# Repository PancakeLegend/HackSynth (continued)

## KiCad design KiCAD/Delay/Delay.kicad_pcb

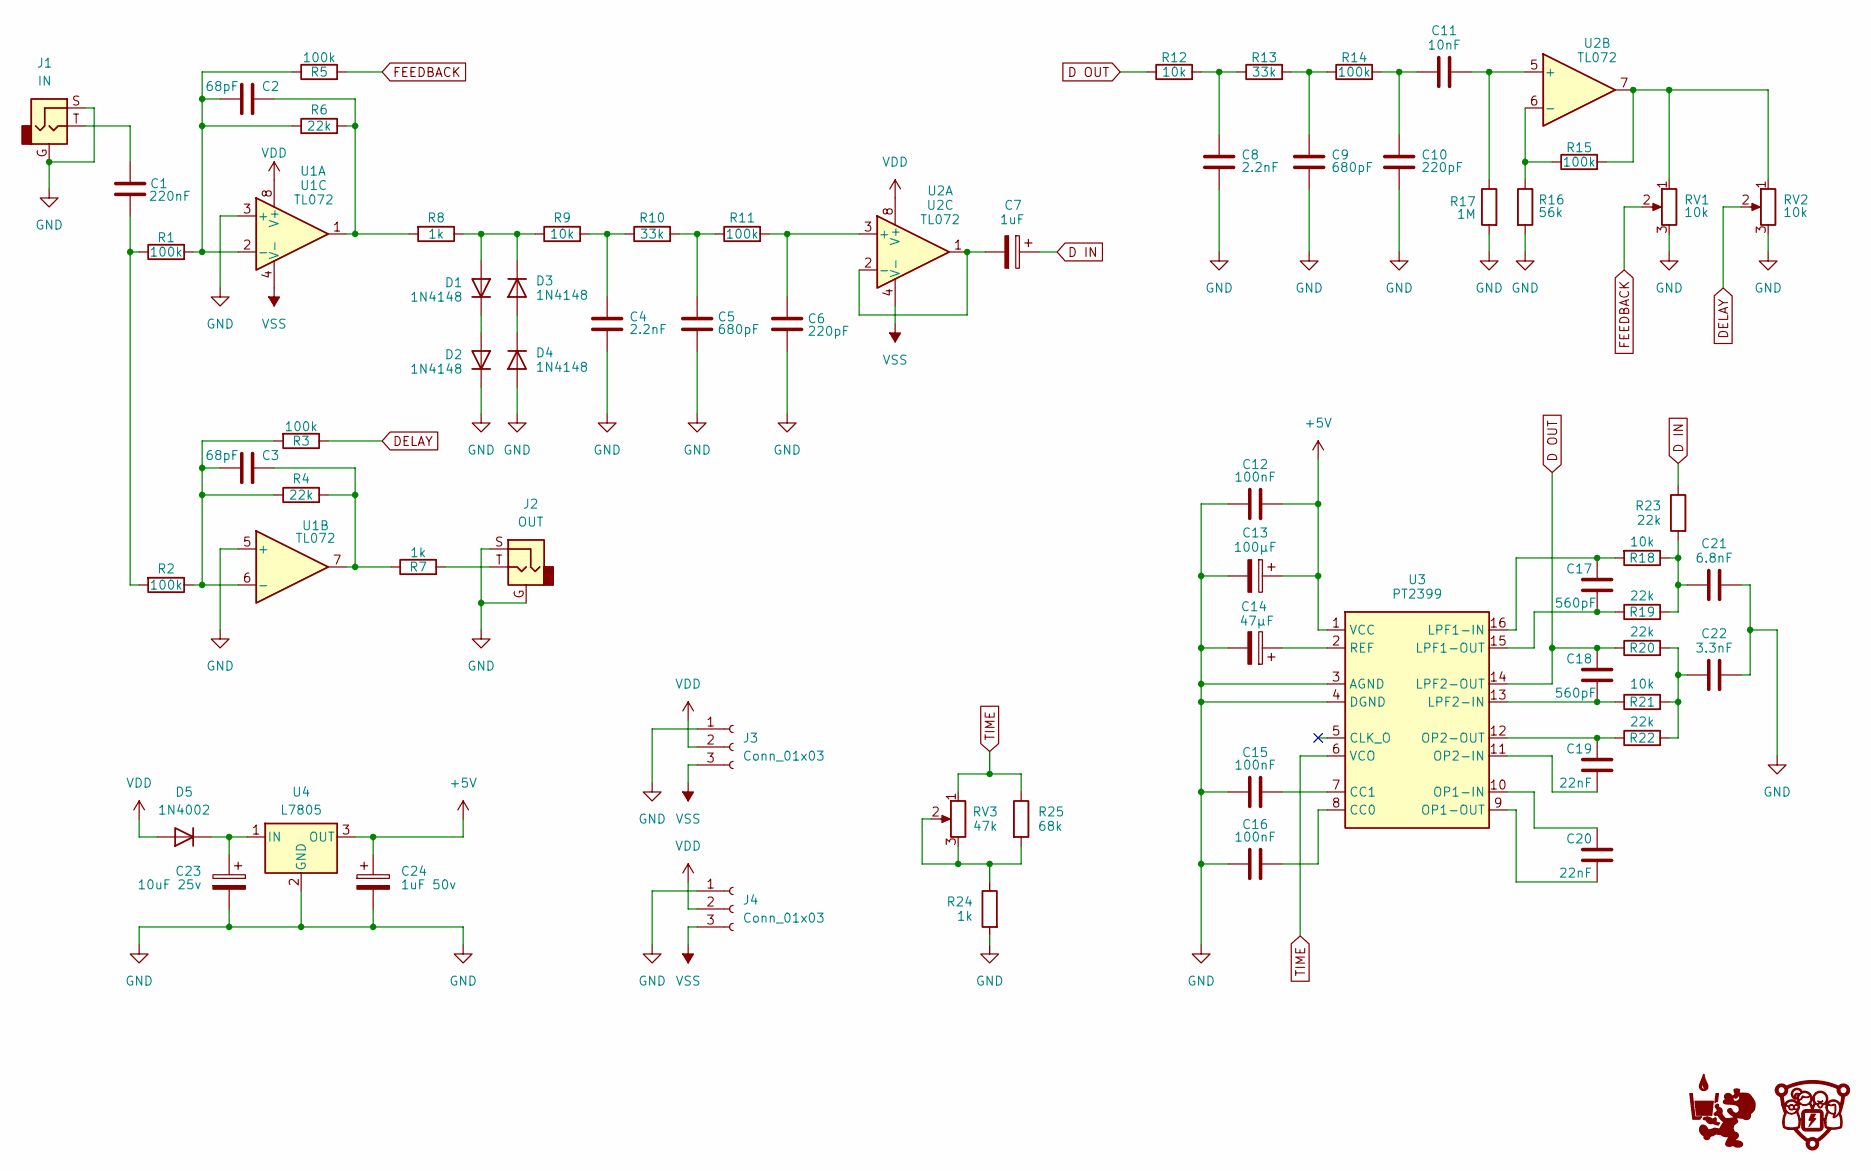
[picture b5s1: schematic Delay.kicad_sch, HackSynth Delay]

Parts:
C1: 220nF; C_Ceramic_D4.5mm_P5.00mm
C2, C3: 68pF; C_Ceramic_D4.5mm_P5.00mm
C4, C8: 2.2nF; C_Ceramic_D4.5mm_P5.00mm
C5, C9: 680pF; C_Ceramic_D4.5mm_P5.00mm
C6, C10: 220pF; C_Ceramic_D4.5mm_P5.00mm
C7: 1uF; CP_Radial_D4.0mm_P1.50mm
C11: 10nF; C_Ceramic_D4.5mm_P5.00mm
C12, C15, C16: 100nF; C_Ceramic_D4.5mm_P5.00mm
C13: 100µF; CP_Radial_D5.2mm_P2.50mm_LayDown_Mirror
C14: 47µF; CP_Radial_D5.2mm_P2.50mm_LayDown
C17, C18: 560pF; C_Ceramic_D4.5mm_P5.00mm
C19, C20: 22nF; C_Ceramic_D4.5mm_P5.00mm
C21: 6.8nF; C_Disc_D7.5mm_W5.0mm_P7.50mm
C22: 3.3nF; C_Disc_D7.5mm_W5.0mm_P7.50mm
C23: 10uF 25v; CP_Radial_D4.0mm_P1.50mm
C24: 1uF 50v; CP_Radial_D4.0mm_P1.50mm
D1, D2, D3, D4: 1N4148; D_Vertical_P2.54mm
D5: 1N4002; D_A-405_P7.62mm_Horizontal
G1, G2: (no value)
J1: IN; Jack_3.5mm
J2: OUT; Jack_3.5mm
J3, J4: Conn_01x03; JST_PH_S3B-PH-K_1x03_P2.00mm_Horizontal
R1, R2, R3, R5, R11, R14, R15: 100k; R_Vertical_P2.54mm
R4, R6, R19, R20, R22, R23: 22k; R_Vertical_P2.54mm
R7, R8, R24: 1k; R_Vertical_P2.54mm
R9, R12, R18, R21: 10k; R_Vertical_P2.54mm
R10, R13: 33k; R_Vertical_P2.54mm
R16: 56k; R_Vertical_P2.54mm
R17: 1M; R_Vertical_P2.54mm
R25: 68k; R_Vertical_P2.54mm
RV1, RV2: 10k; Potentiometer_Alps_RK09K_Horizontal
RV3: 47k; Potentiometer_Alps_RK09K_Horizontal
U1, U2: TL072; DIP-8_W7.62mm_LongPads
U3: PT2399; DIP-16_W7.62mm_LongPads
U4: L7805; L7805 - TO-220-3_Horizontal_TabDown

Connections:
+5V: C12.1, C13.1, C24.1, U3.1 (VCC), U4.3 (OUT)
D IN: C7.1, R23.1
D OUT: C18.1, R12.1, R20.1, U3.14 (LPF2-OUT)
DELAY: R3.1, RV2.2
FEEDBACK: R5.2, RV1.2
GND: C4.2, C5.2, C6.2, C8.2, C9.2, C10.2, C12.2, C13.2, C14.2, C15.2, C16.2, C21.1, C22.1, C23.2, C24.2, D2.1 (K), D4.2 (A), J1.G, J1.S, J2.G, J2.S, J3.1, J4.1, R16.2, R17.2, R24.2, RV1.3, RV2.3, U1.3 (+), U1.5 (+), U3.3 (AGND), U3.4 (DGND), U4.2 (GND)
unnamed: C1.1, R1.1, R2.2
unnamed: C1.2, J1.T
unnamed: C2.1, R6.2, R8.2, U1.1
unnamed: C3.1, R4.2, R7.1, U1.7
unnamed: C4.1, R9.2, R10.1
unnamed: C5.1, R10.2, R11.1
unnamed: C8.1, R12.2, R13.1
unnamed: C9.1, R13.2, R14.1
unnamed: C10.1, C11.1, R14.2
unnamed: C21.2, R18.1, R19.2, R23.2
unnamed: C22.2, R20.2, R21.2, R22.2
unnamed: D1.2 (A), D3.1 (K), R8.1, R9.1
unnamed: D1.1 (K), D2.2 (A)
unnamed: D3.2 (A), D4.1 (K)
unnamed: C23.1, D5.1 (K), U4.1 (IN)
unnamed: J2.T, R7.2
unnamed: R15.2, RV1.1, RV2.1, U2.7
unnamed: R24.1, R25.2, RV3.2, RV3.3
unnamed: C2.2, R1.2, R5.1, R6.1, U1.2 (-)
unnamed: C3.2, R2.1, R3.2, R4.1, U1.6 (-)
unnamed: C6.1, R11.2, U2.3 (+)
unnamed: C7.2, U2.1, U2.2 (-)
unnamed: C11.2, R17.1, U2.5 (+)
unnamed: R15.1, R16.1, U2.6 (-)
unnamed: C16.1, U3.8 (CC0)
unnamed: C15.1, U3.7 (CC1)
unnamed: C17.1, R18.2, U3.16 (LPF1-IN)
unnamed: C17.2, R19.1, U3.15 (LPF1-OUT)
unnamed: C18.2, R21.1, U3.13 (LPF2-IN)
unnamed: C20.1, U3.10 (OP1-IN)
unnamed: C20.2, U3.9 (OP1-OUT)
unnamed: C19.2, U3.11 (OP2-IN)
unnamed: C19.1, R22.1, U3.12 (OP2-OUT)
unnamed: C14.1, U3.2 (REF)
TIME: R25.1, RV3.1, U3.6 (VCO)
VDD: D5.2 (A), J3.2, J4.2, U1.8 (V+), U2.8 (V+)
VSS: J3.3, J4.3, U1.4 (V-), U2.4 (V-)

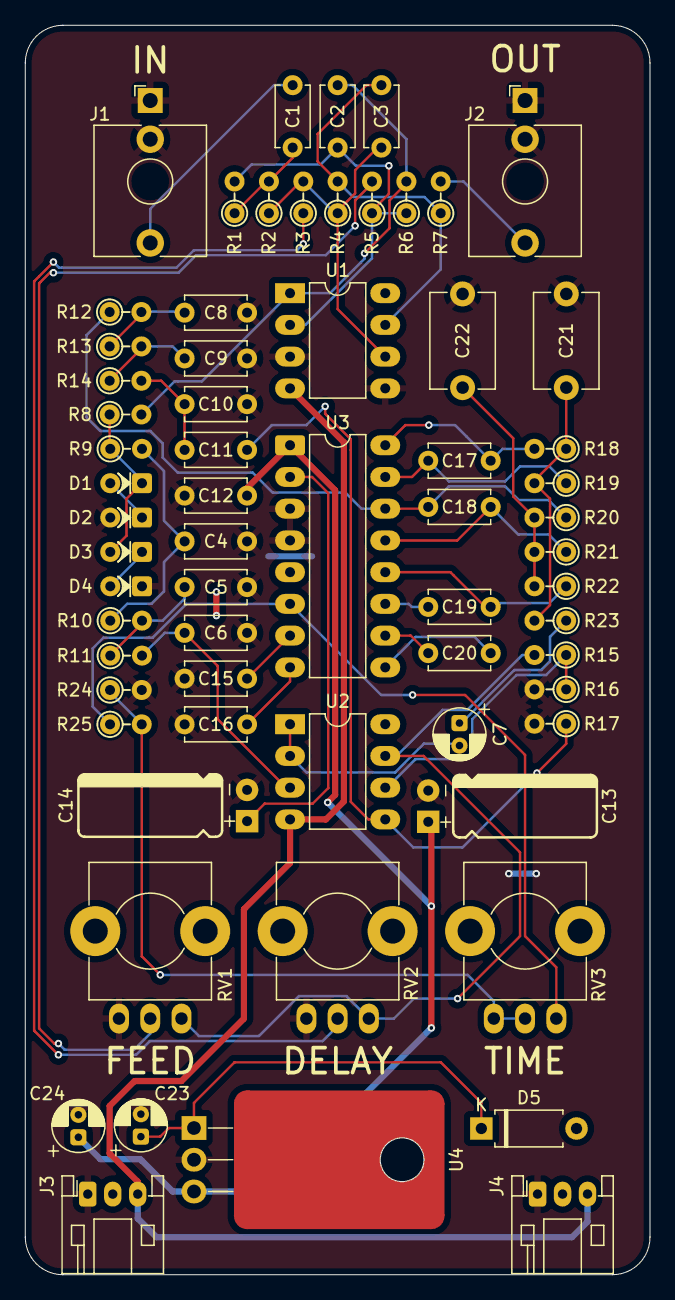
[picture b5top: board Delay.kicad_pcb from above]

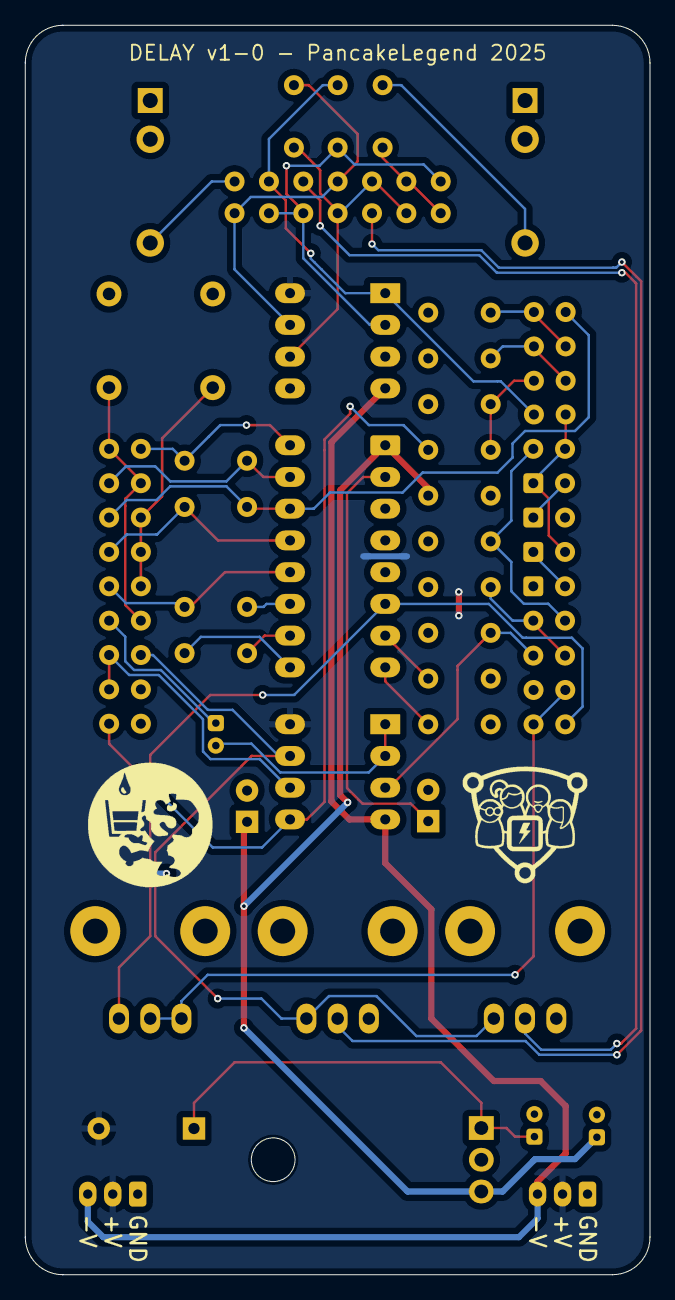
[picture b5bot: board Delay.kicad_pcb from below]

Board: 2 copper layers, 50.0 x 100.0 mm, 67 parts (2 on the bottom side), 43 nets.

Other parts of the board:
Ref**: Val**; Logo - PancakeLegend 10mm
Ref**#2: Val**; Logo - CCHS 10mm

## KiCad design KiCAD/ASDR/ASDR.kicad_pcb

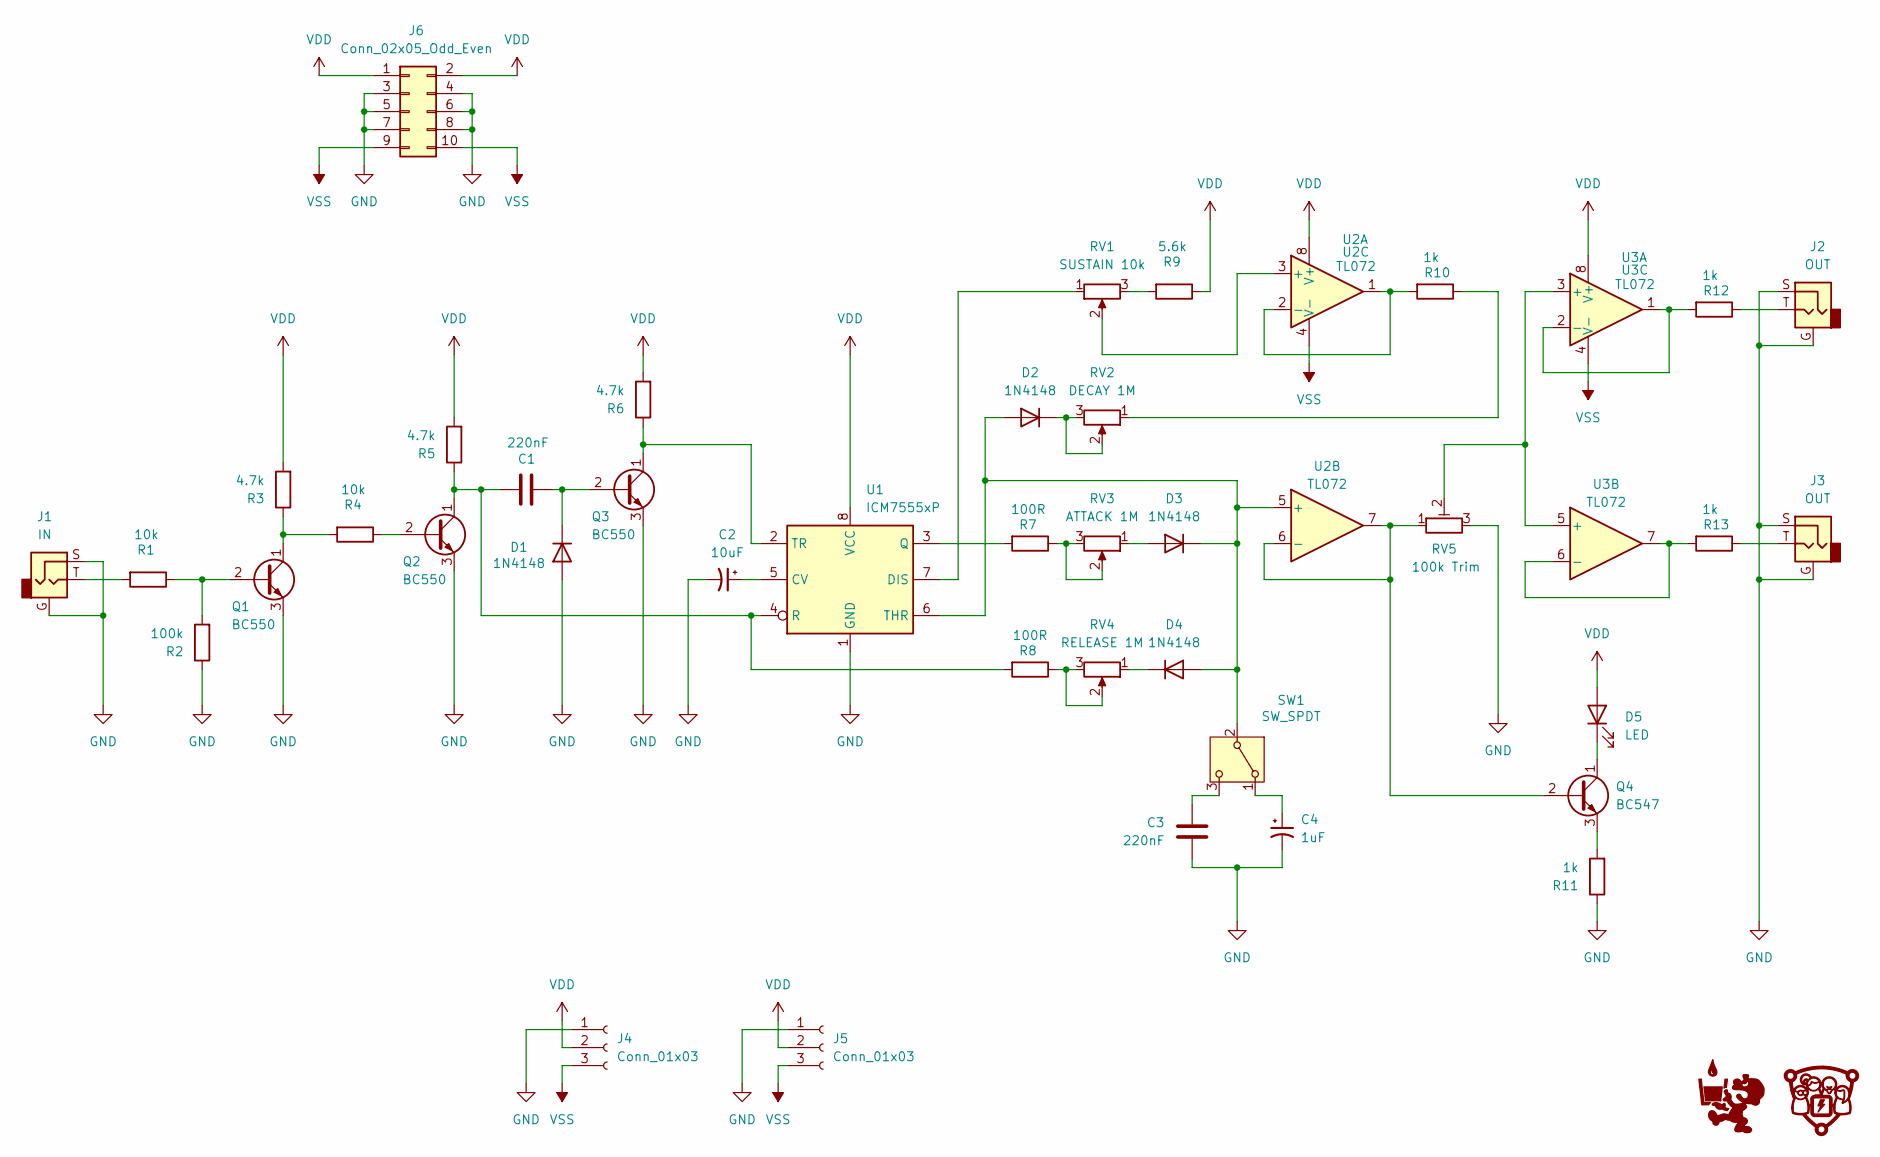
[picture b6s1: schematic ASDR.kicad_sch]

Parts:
C1, C3: 220nF; C_Ceramic_D4.5mm_P5.00mm
C2: 10uF; CP_Radial_D4.0mm_P1.50mm
C4: 1uF; C_Ceramic_D4.5mm_P5.00mm
D1, D2, D3, D4: 1N4148; D_DO-35_SOD27_P7.62mm_Horizontal
D5: LED; LED_D5.0mm
G1, G2: (no value)
J1: IN; Jack_3.5mm
J2, J3: OUT; Jack_3.5mm
J4, J5: Conn_01x03; JST_PH_S3B-PH-K_1x03_P2.00mm_Horizontal
J6: Conn_02x05_Odd_Even
Q1, Q2, Q3: BC550; TO-92_Inline - Handsolder
Q4: BC547; TO-92_Inline - Handsolder
R1, R4: 10k; R_Axial_DIN0207_L6.3mm_D2.5mm_P7.62mm_Horizontal
R2: 100k; R_Axial_DIN0207_L6.3mm_D2.5mm_P7.62mm_Horizontal
R3, R5, R6: 4.7k; R_Axial_DIN0207_L6.3mm_D2.5mm_P7.62mm_Horizontal
R7, R8: 100R; R_Axial_DIN0207_L6.3mm_D2.5mm_P7.62mm_Horizontal
R9: 5.6k; R_Axial_DIN0207_L6.3mm_D2.5mm_P7.62mm_Horizontal
R10, R11, R12, R13: 1k; R_Axial_DIN0207_L6.3mm_D2.5mm_P7.62mm_Horizontal
RV1: SUSTAIN 10k; Potentiometer_Alps_RK09K_Horizontal
RV2: DECAY 1M; Potentiometer_Alps_RK09K_Horizontal
RV3: ATTACK 1M; Potentiometer_Alps_RK09K_Horizontal
RV4: RELEASE 1M; Potentiometer_Alps_RK09K_Horizontal
RV5: 100k Trim; TrimPot_Bourns_3339S_Horizontal
SW1: SW_SPDT; Switch SPDT - MTS-102
U1: ICM7555xP; DIP-8_W7.62mm_LongPads
U2, U3: TL072; DIP-8_W7.62mm_LongPads

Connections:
GND: C2.2, C3.2, C4.2, D1.2 (A), J1.G, J1.S, J2.G, J2.S, J3.G, J3.S, J4.1, J5.1, J6.3, J6.4, J6.5, J6.6, J6.7, J6.8, Q1.3 (E), Q2.3 (E), Q3.3 (E), R2.1, R11.1, RV5.3, U1.1 (GND)
unnamed: C1.1, D1.1 (K), Q3.2 (B)
unnamed: D2.2 (A), D3.1 (K), D4.2 (A), SW1.2 (B), U1.6 (THR), U2.5 (+)
unnamed: D2.1 (K), RV2.2, RV2.3
unnamed: D3.2 (A), RV3.1
unnamed: D4.1 (K), RV4.1
unnamed: D5.1 (K), Q4.1 (C)
unnamed: J1.T, R1.2
unnamed: J2.T, R12.1
unnamed: J3.T, R13.1
unnamed: Q1.2 (B), R1.1, R2.2
unnamed: Q1.1 (C), R3.1, R4.2
unnamed: Q2.2 (B), R4.1
unnamed: C1.2, Q2.1 (C), R5.1, R8.2, U1.4 (R)
unnamed: Q3.1 (C), R6.1, U1.2 (TR)
unnamed: Q4.2 (B), RV5.1, U2.6 (-), U2.7
unnamed: Q4.3 (E), R11.2
unnamed: R7.1, RV3.2, RV3.3
unnamed: R8.1, RV4.2, RV4.3
unnamed: R9.2, RV1.3
unnamed: R10.1, RV2.1
unnamed: C4.1, SW1.1 (A)
unnamed: C3.1, SW1.3 (C)
unnamed: C2.1, U1.5 (CV)
unnamed: RV1.1, U1.7 (DIS)
unnamed: R7.2, U1.3 (Q)
unnamed: RV1.2, U2.3 (+)
unnamed: R10.2, U2.1, U2.2 (-)
unnamed: RV5.2, U3.3 (+), U3.5 (+)
unnamed: R12.2, U3.1, U3.2 (-)
unnamed: R13.2, U3.6 (-), U3.7
VDD: D5.2 (A), J4.2, J5.2, J6.1, J6.2, R3.2, R5.2, R6.2, R9.1, U1.8 (VCC), U2.8 (V+), U3.8 (V+)
VSS: J4.3, J5.3, J6.9, J6.10, U2.4 (V-), U3.4 (V-)

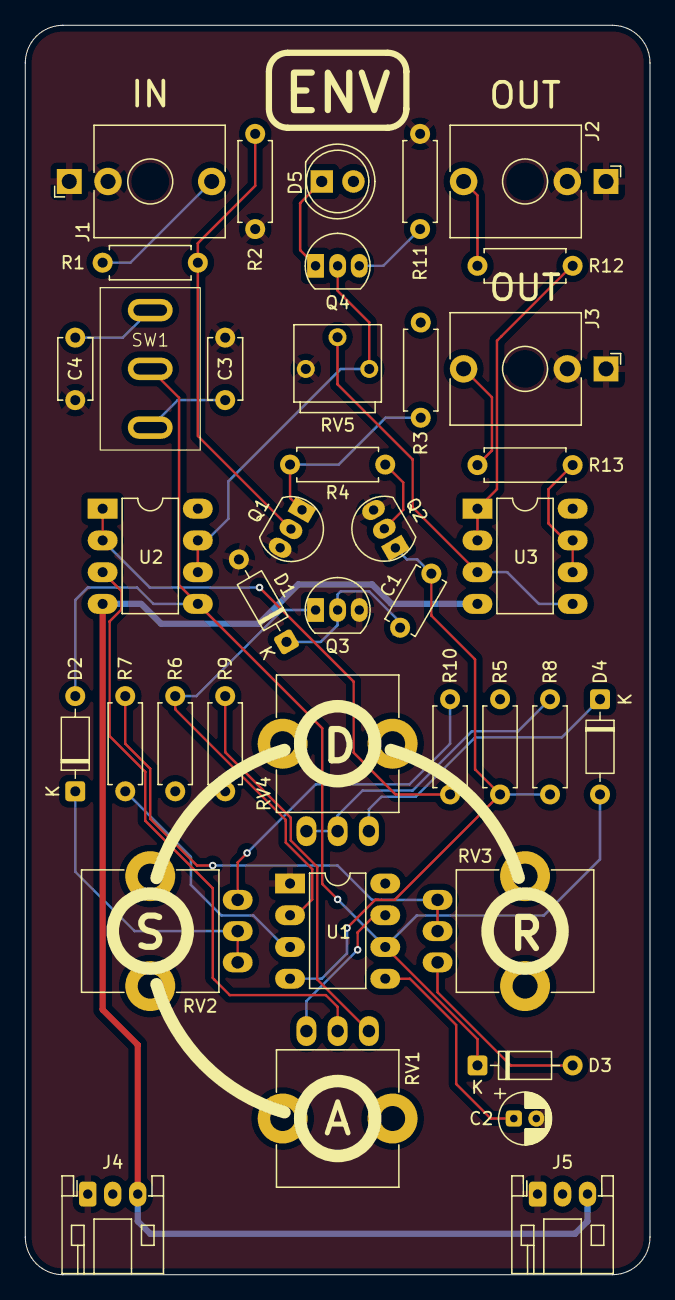
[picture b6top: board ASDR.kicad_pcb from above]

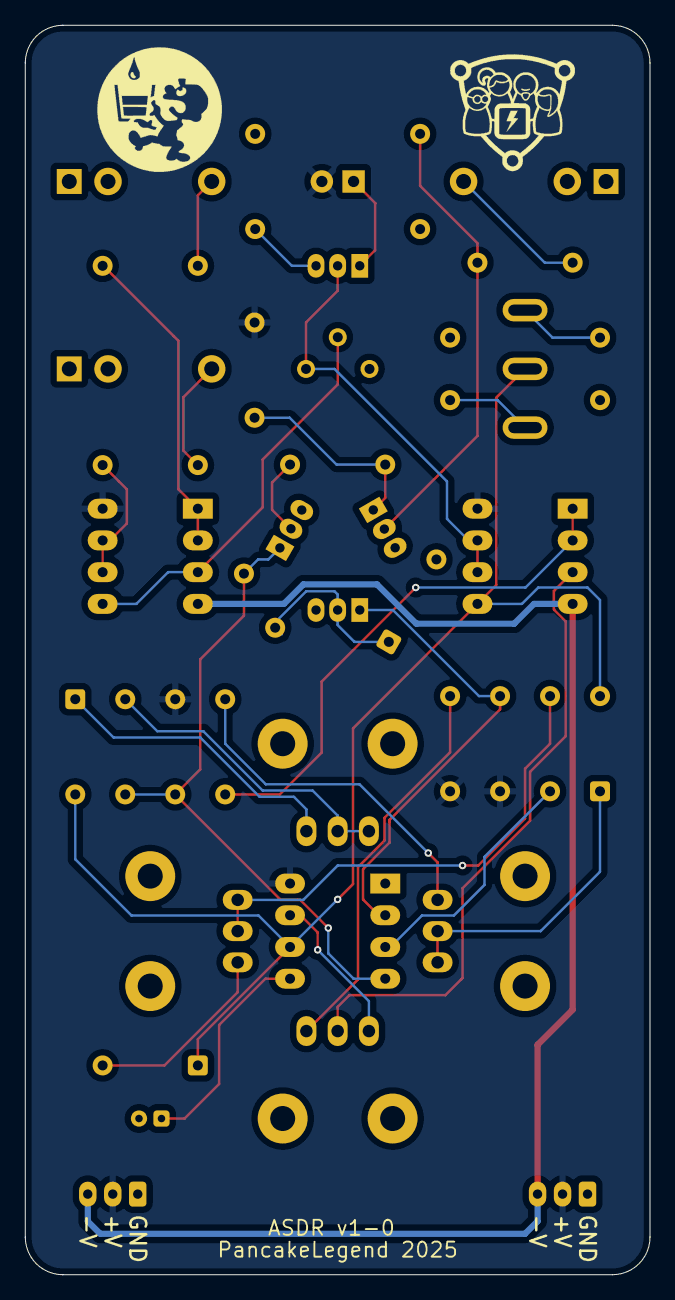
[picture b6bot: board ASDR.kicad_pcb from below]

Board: 2 copper layers, 50.0 x 100.0 mm, 42 parts (2 on the bottom side), 33 nets.

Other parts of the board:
Ref**: Val**; PancakeLegend Logo - 10mm
Ref**#2: Val**; CCHS Logo - 10mm

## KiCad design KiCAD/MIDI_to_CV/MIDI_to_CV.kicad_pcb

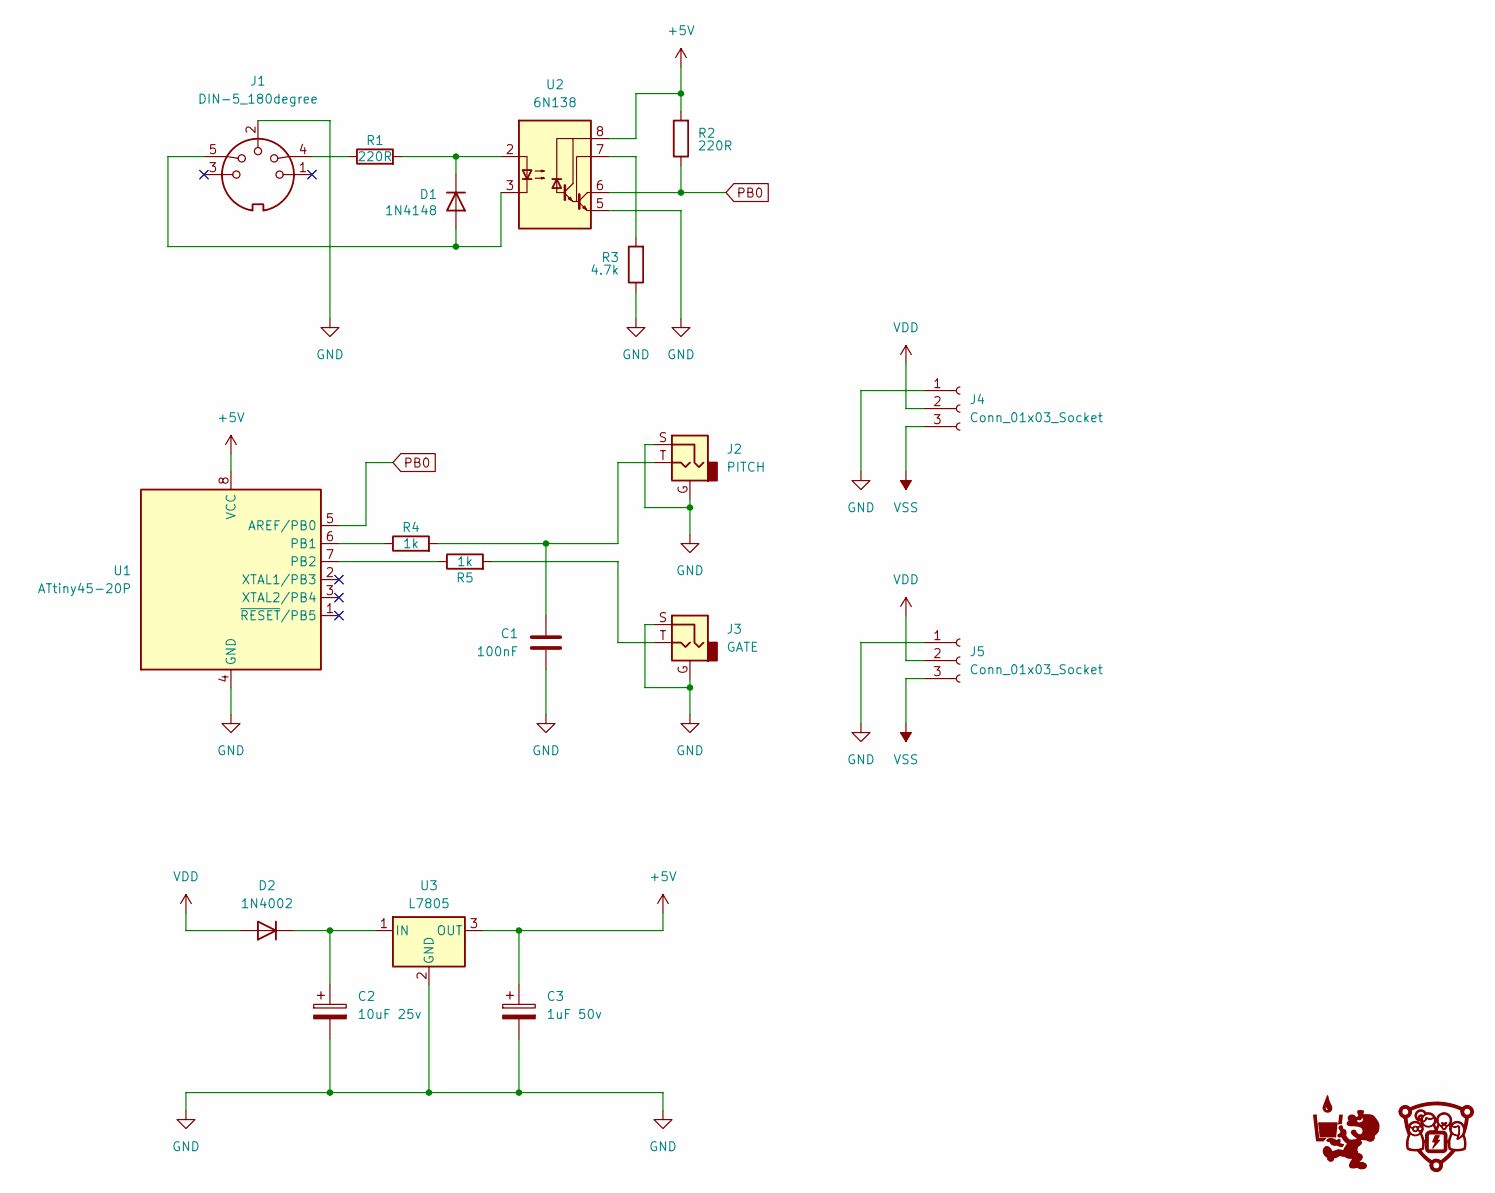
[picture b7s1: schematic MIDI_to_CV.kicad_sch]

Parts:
C1: 100nF; C_Disc_D5.0mm_W2.5mm_P5.00mm
C2: 10uF 25v; CP_Radial_D4.0mm_P1.50mm
C3: 1uF 50v; CP_Radial_D4.0mm_P1.50mm
D1: 1N4148; D_DO-35_SOD27_P7.62mm_Horizontal
D2: 1N4002; D_A-405_P7.62mm_Horizontal
G1, G2: (no value)
J1: DIN-5_180degree; DIN-5 - DS-5-07A - MIDI Jack
J2: PITCH; Jack_3.5mm
J3: GATE; Jack_3.5mm
J4, J5: Conn_01x03_Socket; JST_PH_S3B-PH-K_1x03_P2.00mm_Horizontal
R1, R2: 220R; R_Axial_DIN0207_L6.3mm_D2.5mm_P7.62mm_Horizontal
R3: 4.7k; R_Axial_DIN0207_L6.3mm_D2.5mm_P7.62mm_Horizontal
R4, R5: 1k; R_Axial_DIN0207_L6.3mm_D2.5mm_P7.62mm_Horizontal
U1: ATtiny45-20P; DIP-8_W7.62mm_LongPads
U2: 6N138; DIP-8_W7.62mm_LongPads
U3: L7805; L7805 - TO-220-3_Horizontal_TabDown

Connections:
+5V: C3.1, R2.2, U1.8 (VCC), U2.8 (VCC), U3.3 (OUT)
GND: C1.2, C2.2, C3.2, J1.2, J2.G, J2.S, J3.G, J3.S, J4.1, J5.1, R3.1, U1.4 (GND), U2.5 (GND), U3.2 (GND)
unnamed: C1.1, J2.T, R4.2
unnamed: D1.2 (A), J1.5, U2.3 (C2)
unnamed: D1.1 (K), R1.2, U2.2 (C1)
unnamed: C2.1, D2.1 (K), U3.1 (IN)
unnamed: J1.4, R1.1
unnamed: J3.T, R5.2
unnamed: R4.1, U1.6 (PB1)
unnamed: R5.1, U1.7 (PB2)
unnamed: R3.2, U2.7 (VO1)
PB0: R2.1, U1.5 (AREF/PB0), U2.6 (VO2)
VDD: D2.2 (A), J4.2, J5.2
VSS: J4.3, J5.3

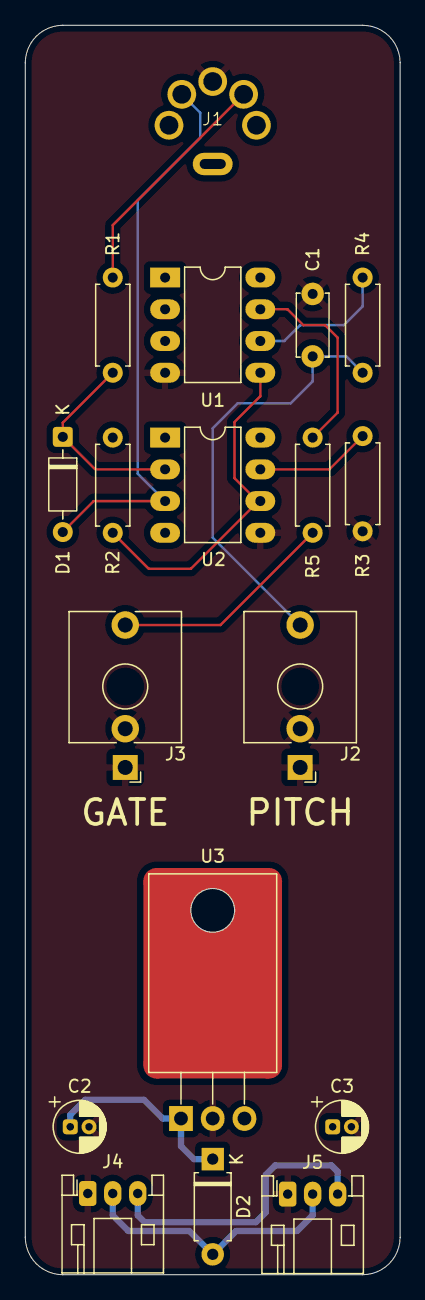
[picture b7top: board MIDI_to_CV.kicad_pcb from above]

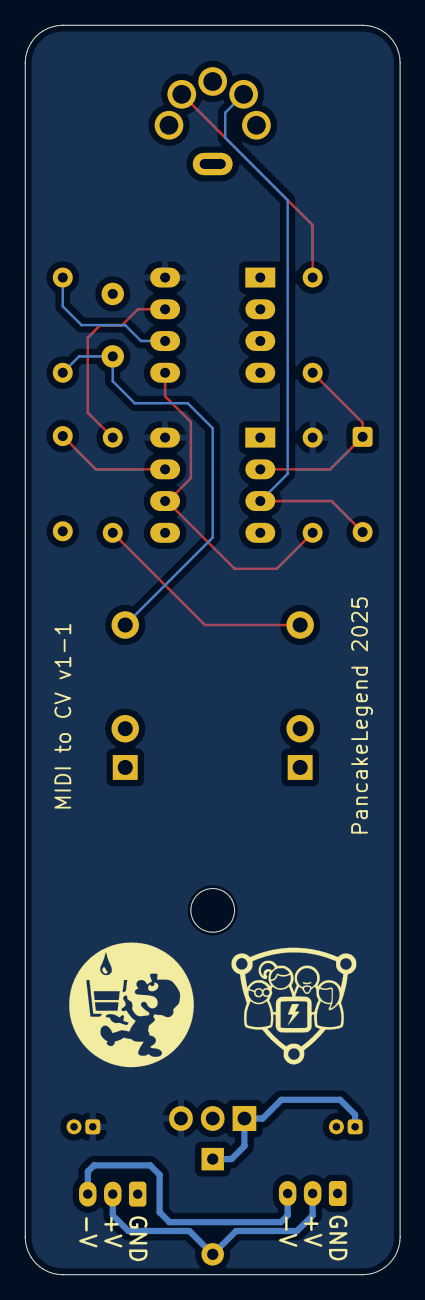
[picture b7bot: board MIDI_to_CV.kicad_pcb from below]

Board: 2 copper layers, 30.0 x 100.0 mm, 20 parts (2 on the bottom side), 14 nets.

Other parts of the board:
Ref**: Val**; CCHS Logo - 10mm
Ref**#2: Val**; PancakeLegend Logo - 10mm

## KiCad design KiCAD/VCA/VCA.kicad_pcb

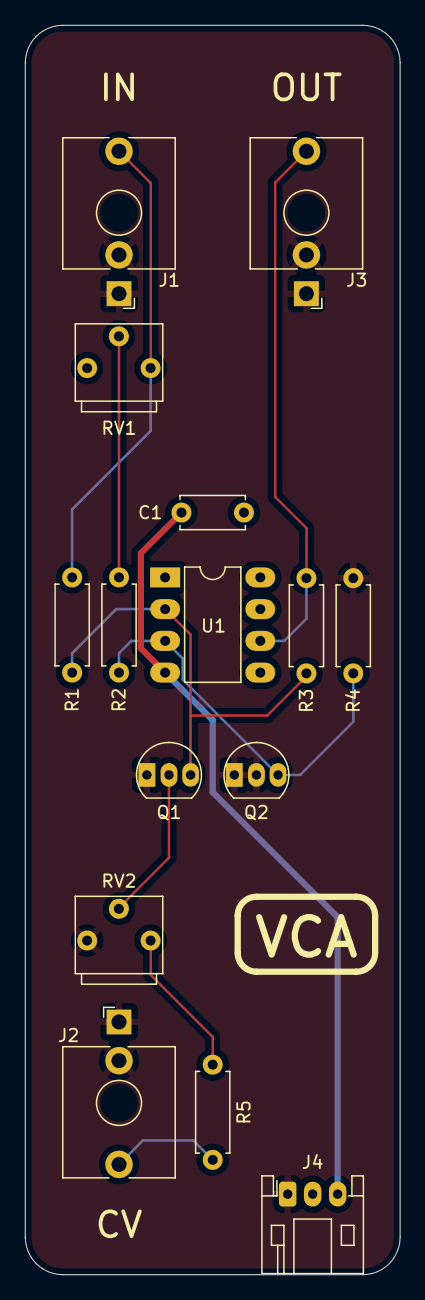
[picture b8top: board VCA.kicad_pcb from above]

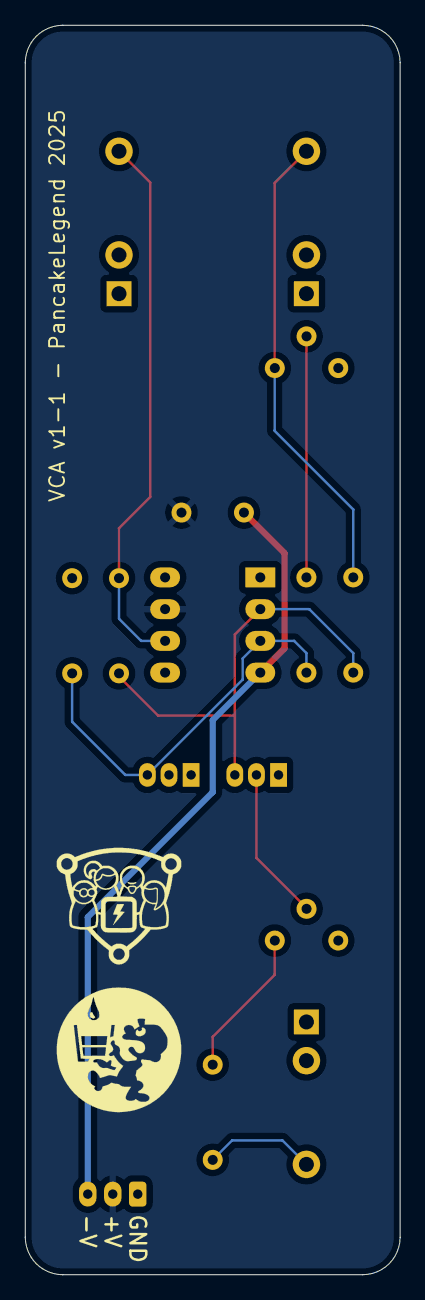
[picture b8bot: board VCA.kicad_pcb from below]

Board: 2 copper layers, 30.0 x 100.0 mm, 17 parts (2 on the bottom side), 11 nets.

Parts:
C1: C; C_Disc_D5.0mm_W2.5mm_P5.00mm
J1: VIN; Jack_3.5mm
J2: VC; Jack_3.5mm
J3: VOUT; Jack_3.5mm
J4: Conn_01x03_Pin; JST_PH_S3B-PH-K_1x03_P2.00mm_Horizontal
Q1, Q2: J172; J172_TO-92_Inline - Handsolder
R1, R2, R3, R4: 10k; R_Axial_DIN0207_L6.3mm_D2.5mm_P7.62mm_Horizontal
R5: 27k; R_Axial_DIN0207_L6.3mm_D2.5mm_P7.62mm_Horizontal
RV1: 1kΩ TrimPot; TrimPot_Bourns_3339S_Horizontal
RV2: 100kΩ TrimPot; TrimPot_Bourns_3339S_Horizontal
Ref**: Val**; PancakeLegend Logo - 10mm
Ref**#2: Val**; CCHS Logo - 10mm
U1: LT1006; DIP-8_W7.62mm_LongPads

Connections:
GND: J1.G, J1.S, J2.G, J2.S, J3.G, J3.S, J4.1, Q1.3 (S), Q2.2 (G), Q2.3 (S), R4.2, RV2.3
unnamed: J1.T, R1.1, RV1.1
unnamed: J2.T, R5.1
unnamed: J3.T, R3.2, U1.6
unnamed: Q1.1 (D), R1.2, R3.1, U1.2 (-)
unnamed: Q1.2 (G), RV2.2
unnamed: Q2.1 (D), R2.2, R4.1, U1.3 (+)
unnamed: R2.1, RV1.2
unnamed: R5.2, RV2.1
VDD: C1.1, J4.2, U1.7 (V+)
VSS: C1.2, J4.3, U1.4 (V-)

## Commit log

2025-04-25 Initial
2025-04-25 Backups
2025-05-08 commenced VCO schematic.
2025-05-09 Library additions
2025-05-11 Library updates
2025-05-15 VCO Schematic Backups
2025-05-15 Add footprint library components.
2025-05-16 VCO and Power updates
2025-05-18 Power Schematic and Libraries
2025-05-18 MidMount Capacitors
2025-05-18 VCA Schematic
2025-05-18 Notes
2025-05-18 Power PCB
2025-05-20 VCA PCB Start
2025-05-21 Power PCB Gerbers
2025-05-23 VCA PCB
2025-05-23 3.5mm Jack
2025-05-24 Power PCB Cleanup
2025-05-31 VCA Gerbers
2025-05-31 Cap 3D Model Updates
2025-05-31 Footprint Update
2025-06-05 Mid VCO pcb session.
2025-06-07 Logos Added
2025-06-07 VCO Board Setup
    Set up net classes and removed additional layers
2025-06-08 Make VCA 2-Layer
2025-06-08 MIDI to CV Schematic
    Heavy lifting done. Started on PCB Layout.
2025-06-08 MIDI to CV - PCB Placement
2025-06-08 MIDI to CV - PCB
2025-06-09 MIDI Jack Footprint
2025-06-09 MIDI to CV - Gerbers
2025-06-09 VCA - Minor Trace Edit
2025-06-10 Mixer Schematic
2025-06-11 Mixer Footprint Association
2025-06-13 Mixer PCB
2025-06-14 Mixer PCB - Gerbers
2025-06-14 LFO Schematic
2025-06-14 LFO PCB
2025-06-14 ASDR Schematic + LFO Gerbers
2025-06-14 ADSR PCB
2025-06-15 Review
2025-06-15 VCF Schematic
2025-06-15 VCF PCB Start
2025-06-15 VCO PCB Resistor alignment.
2025-06-15 VCO rearrange pcb
2025-06-15 Vertical Resistor Footprint
2025-06-15 VCO pcb board population persists
2025-06-16 ASDR PCB
2025-06-16 Minor VCO update
2025-06-17 VCA Footprint update
2025-06-18 ADSR Rearrange
2025-06-18 VCF PCB
2025-06-20 MIDI to CV Cap Footprint Change
2025-06-20 VCF Reorg
2025-06-21 VCF Gerbers
2025-06-22 Delay PCB
2025-06-23 Ignore .lck files.
2025-06-23 Reapply VCO pcb layout changes.
2025-06-24 Backup Cleanup
2025-06-26 Make the transistors touch
2025-06-27 LFO v1-1
2025-06-27 Add a cap to pin 13
2025-06-29 Footprint Edits
2025-06-30 Chorus Schematic
2025-07-01 Rework VCO traces.
2025-07-01 Bring jack back in line with grid
2025-07-01 Chorus PCB Dread + Footprint Edit
2025-07-01 Clean up text references on VCO
2025-07-03 remove unnecessary tracks
2025-07-04 Chorus PCB Start
2025-07-05 Chorus Trace Begin
2025-07-05 Chorus Trace v1
2025-07-05 Chorus Legends
2025-07-06 Chorus DRC
2025-07-10 Rearrange text and add labels
2025-07-10 Adjustments to labels
2025-07-24 Cleanup resistor references etc
2025-07-26 Chorus Backups
2025-07-26 Fixing tracework
2025-07-28 Ignore Project Files
2025-07-31 Chorus Gerbers
2025-07-31 Fix isolated VDD region
2025-07-31 Create gerber files
2025-07-31 Send gerbers to compressed file and add order settings
2025-08-28 Fix missing resistor values
2025-09-19 Power v1-2
2026-01-15 Update README.md
    Update README.md
2026-01-23 Fixes
2026-02-01 Sync
2026-02-01 VCO v1-1 Created
2026-02-02 Gerbers
2026-02-02 Gerbers - Minor Edits
2026-02-02 Backup
